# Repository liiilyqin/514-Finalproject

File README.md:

# 514-Finalproject--Sound Detector in Clubs

# Current Situation
In many clubs, loud and intense music is commonly played to create an energetic atmosphere that helps people relax. However, to enhance this effect, DJs often push the volume to high levels, which can pose serious risks to hearing health. Specifically, prolonged exposure to noise levels of 70-85 dB (e.g., vacuum cleaners) may cause mild hearing damage, levels above 85 dB (e.g., heavy traffic) can harm hearing after 8 hours, exposure to 100 dB (e.g., noisy nightclubs) can affect hearing within 15 minutes, and noise exceeding 120 dB (e.g., airplane engines) poses an immediate risk of permanent damage.

# Proposed Solution
Our project aims to address this issue by using a sound detection sensor that monitors noise levels in clubs. This device will transmit data wirelessly to dispaly device, which visualizes the information using a step motor. When the sound level above the baseline, The system alters DJs, helping to protect people from potential hearing damage. 

## System Architecture
The system includes two devices(sensor device & display device), sensor device use MAX4466 to detect soudn level and transmit it to display device wirelessly through ESP32C3. When the display device recieve data, it will visualize the information through Step motor x27. Also, if the sound level excess the baseline, the LED will turn on to alter people. The button can turn off the light.

## Sensor Device Components  
The sensor device includes a ESP32C3, a sound level detect sensor MAX4466 and a 3.7V 700mAh battery.

## Sensor Device Enclosure
Since the MAX4466 needs microphone to detect data, the enclosure of the sensor device needs a space for microphone to recieve sound data.

## Display Device Components  
The display device includes a ESP32C3, a step motoir x27, a LED, a resistor, a button and a 3.7V 700mAh battery.

## Display Device PCB Design
The ESP32C3 recieve data and send it to step motor and LED. Also, command step motor to visualize the information and control the LED through data and the button.

## Display Device Enclosure
The display device needs a window to show the LED light and need a function to push the button. Also, the enclosure should explain the step motor's visulaization.

## Device communicate  
Materials: sound sensor, PCB, button, battery, gauge, color-coded LED  
Connection: Use PCB to connect and control all the materials. Input sound sensor signals and output different points to gauge, also different color to LED. Use a button to control power from the battery that supplies this device.  
Algorithms:  DSP algorithm to process sound signals

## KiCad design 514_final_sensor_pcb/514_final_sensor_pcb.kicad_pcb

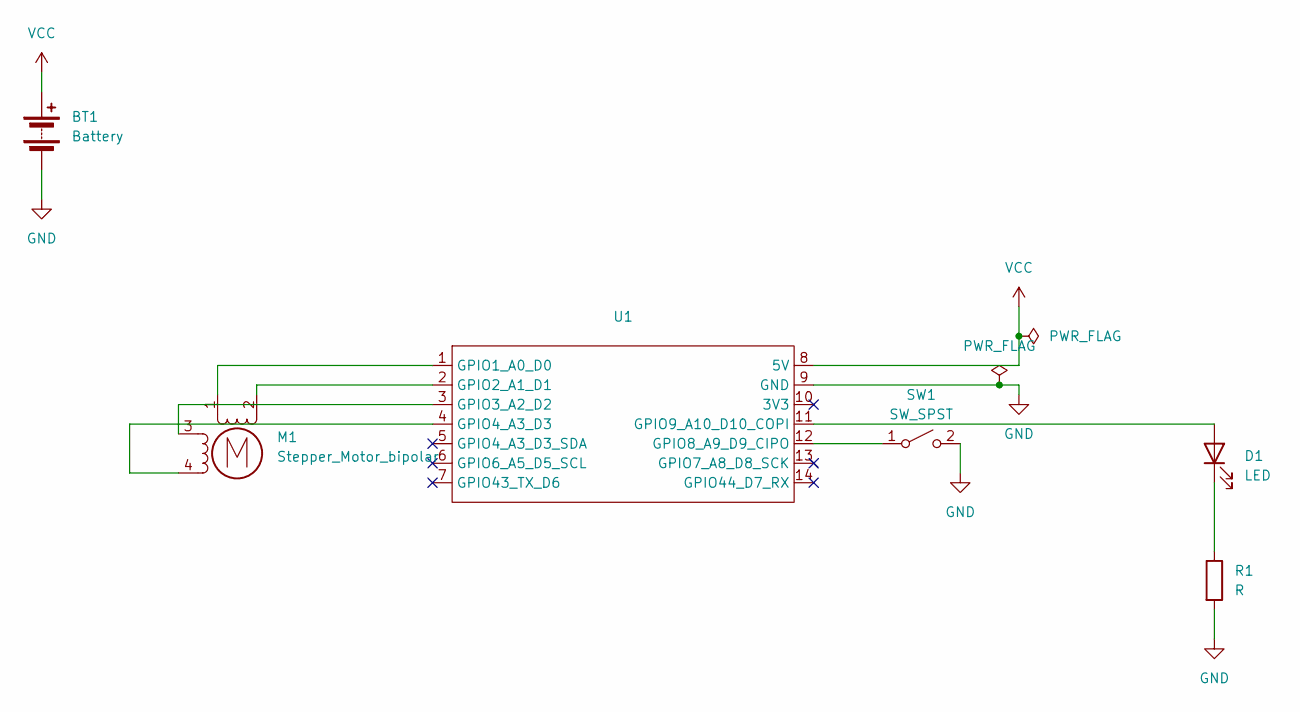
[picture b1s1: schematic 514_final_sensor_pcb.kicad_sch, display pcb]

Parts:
BT1: Battery; JST_PH_B2B-PH-K_1x02_P2.00mm_Vertical
D1: LED; LED_0805_2012Metric_Pad1.15x1.40mm_HandSolder
M1: Stepper_Motor_bipolar; x27_stepper
R1: R; R_0805_2012Metric_Pad1.20x1.40mm_HandSolder
SW1: SW_SPST; SW_PUSH-12mm
U1: XIAO_ESP32_SENSE

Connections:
GND: BT1.2 (-), R1.2, SW1.2 (B), U1.9 (GND)
unnamed: D1.2 (A), U1.11 (GPIO9_A10_D10_COPI)
unnamed: D1.1 (K), R1.1
unnamed: M1.2 (-), U1.2 (GPIO2_A1_D1)
unnamed: SW1.1 (A), U1.12 (GPIO8_A9_D9_CIPO)
unnamed: M1.1, U1.1 (GPIO1_A0_D0)
unnamed: M1.3, U1.3 (GPIO3_A2_D2)
unnamed: M1.4, U1.4 (GPIO4_A3_D3)
VCC: BT1.1 (+), U1.8 (5V)

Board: 2 copper layers, 6 parts (0 on the bottom side), 9 nets, no tracks yet.

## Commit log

2025-01-22 Create picture
2025-01-22 Create s
2025-01-29 Create intro
2025-01-29 Create one
2025-02-14 Create 1
2025-03-10 Create Display Device
2025-03-10 Rename 514 final project system.png to 514 final_project_system.png
